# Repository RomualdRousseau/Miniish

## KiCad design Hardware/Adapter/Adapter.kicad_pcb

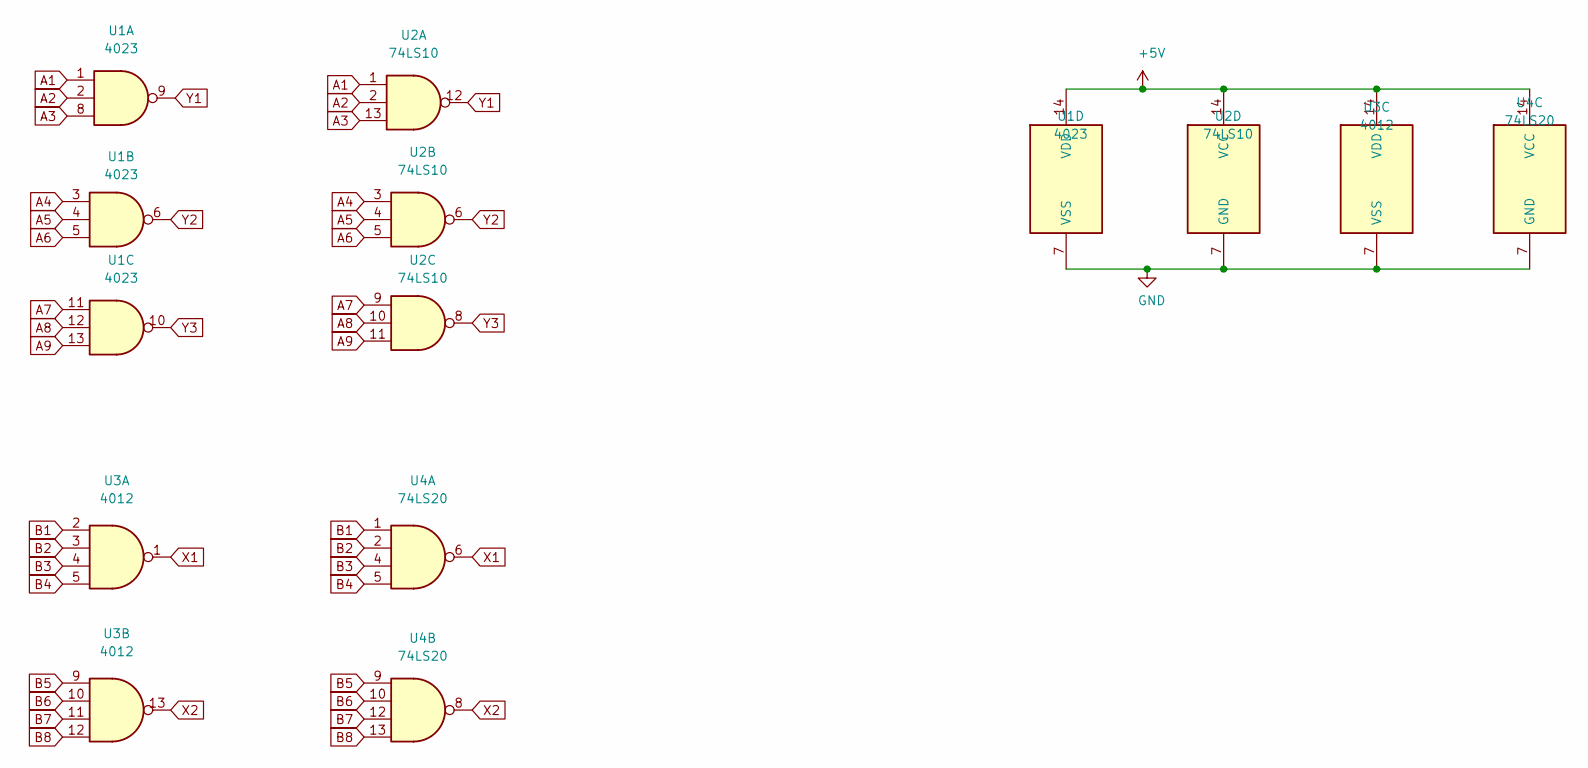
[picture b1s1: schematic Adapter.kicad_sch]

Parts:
U1: 4023; DIP-14_W7.62mm
U2: 74LS10; DIP-14_W7.62mm
U3: 4012; DIP-14_W7.62mm
U4: 74LS20; DIP-14_W7.62mm

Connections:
+5V: U1.14 (VDD), U2.14 (VCC), U3.14 (VDD), U4.14 (VCC)
A1: U1.1, U2.1
A2: U1.2, U2.2
A3: U1.8, U2.13
A4: U1.3, U2.3
A5: U1.4, U2.4
A6: U1.5, U2.5
A7: U1.11, U2.9
A8: U1.12, U2.10
A9: U1.13, U2.11
B1: U3.2, U4.1
B2: U3.3, U4.2
B3: U3.4, U4.4
B4: U3.5, U4.5
B5: U3.9, U4.9
B6: U3.10, U4.10
B7: U3.11, U4.12
B8: U3.12, U4.13
GND: U1.7 (VSS), U2.7 (GND), U3.7 (VSS), U4.7 (GND)
X1: U3.1, U4.6
X2: U3.13, U4.8
Y1: U1.9, U2.12
Y2: U1.6, U2.6
Y3: U1.10, U2.8

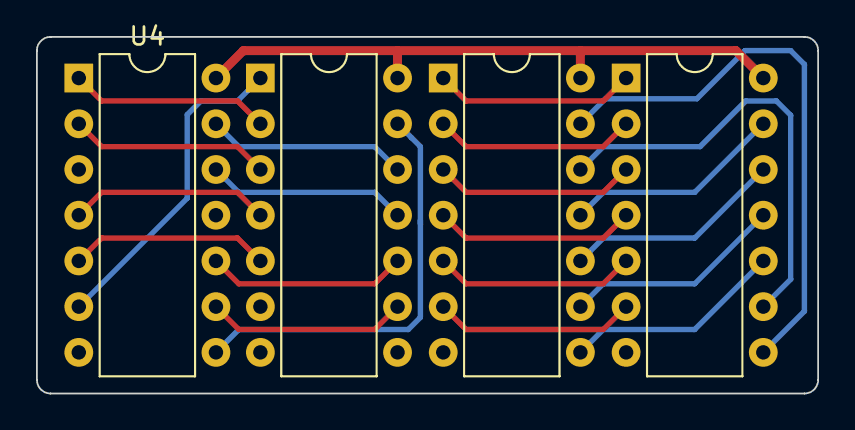
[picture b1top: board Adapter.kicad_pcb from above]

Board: 2 copper layers, 43.4 x 19.8 mm, 4 parts (0 on the bottom side), 24 nets.

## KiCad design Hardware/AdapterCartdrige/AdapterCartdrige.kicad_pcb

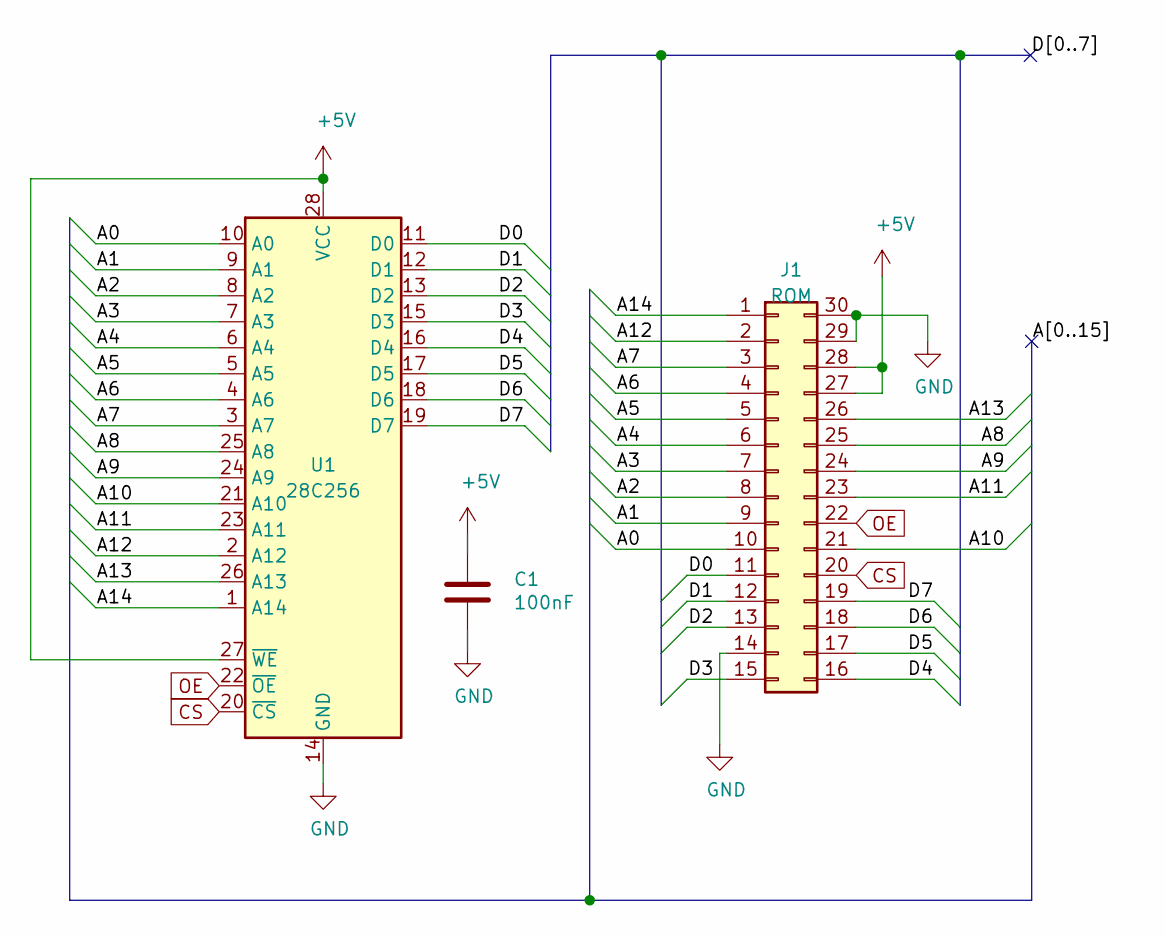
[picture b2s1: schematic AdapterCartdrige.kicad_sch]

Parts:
C1: 100nF; C_Disc_D5.0mm_W2.5mm_P2.50mm
J1: ROM; PinHeader_2x15_P2.54mm_Horizontal
U1: 28C256; DIP-28_W15.24mm

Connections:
+5V: C1.1, J1.27, J1.28, U1.27 (~WE), U1.28 (VCC)
/A0: J1.10, U1.10 (A0)
/A1: J1.9, U1.9 (A1)
/A2: J1.8, U1.8 (A2)
/A3: J1.7, U1.7 (A3)
/A4: J1.6, U1.6 (A4)
/A5: J1.5, U1.5 (A5)
/A6: J1.4, U1.4 (A6)
/A7: J1.3, U1.3 (A7)
/A8: J1.25, U1.25 (A8)
/A9: J1.24, U1.24 (A9)
/A10: J1.21, U1.21 (A10)
/A11: J1.23, U1.23 (A11)
/A12: J1.2, U1.2 (A12)
/A13: J1.26, U1.26 (A13)
/A14: J1.1, U1.1 (A14)
/D0: J1.11, U1.11 (D0)
/D1: J1.12, U1.12 (D1)
/D2: J1.13, U1.13 (D2)
/D3: J1.15, U1.15 (D3)
/D4: J1.16, U1.16 (D4)
/D5: J1.17, U1.17 (D5)
/D6: J1.18, U1.18 (D6)
/D7: J1.19, U1.19 (D7)
CS: J1.20, U1.20 (~CS)
GND: C1.2, J1.14, J1.29, J1.30, U1.14 (GND)
OE: J1.22, U1.22 (~OE)

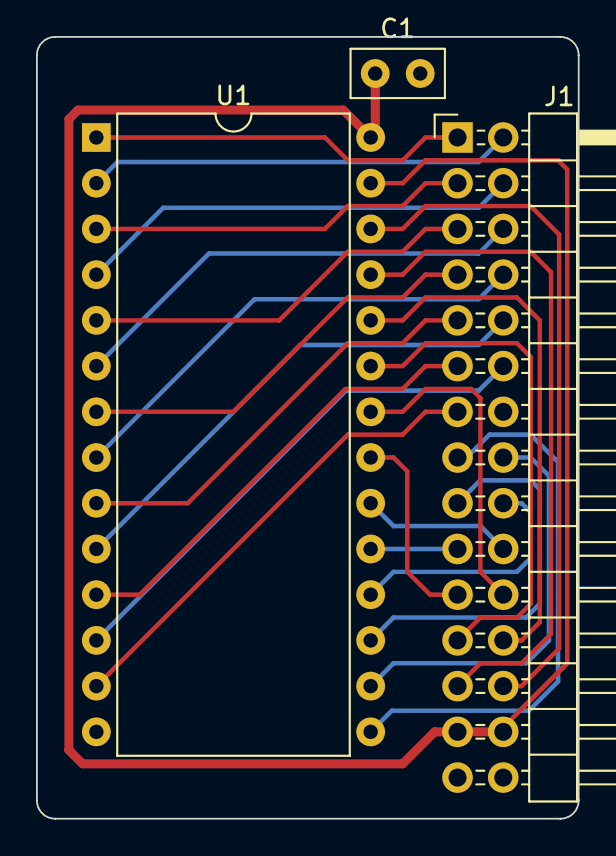
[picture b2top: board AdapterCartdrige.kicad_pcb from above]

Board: 2 copper layers, 30.1 x 43.4 mm, 3 parts (0 on the bottom side), 27 nets.

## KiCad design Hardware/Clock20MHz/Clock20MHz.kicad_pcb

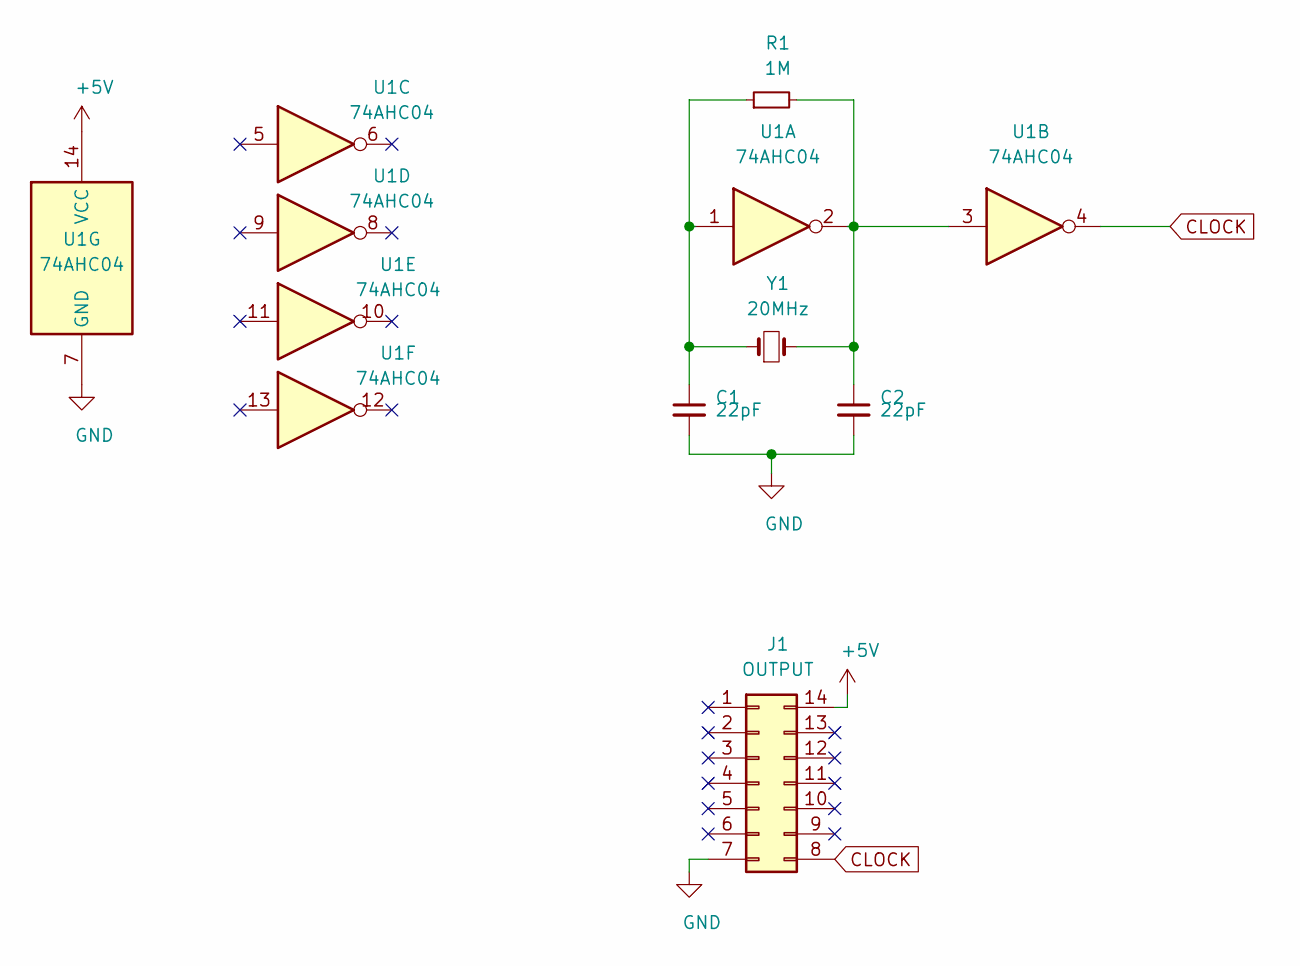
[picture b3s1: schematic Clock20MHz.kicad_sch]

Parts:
C1, C2: 22pF; C_Disc_D5.0mm_W2.5mm_P2.50mm
J1: OUTPUT; DIP-14_W7.62mm
R1: 1M; R_Axial_DIN0207_L6.3mm_D2.5mm_P10.16mm_Horizontal
U1: 74AHC04
Y1: 20MHz; Crystal_HC18-U_Vertical

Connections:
+5V: J1.14, U1.14 (VCC)
CLOCK: J1.8, U1.4
GND: C1.2, C2.2, J1.7, U1.7 (GND)
unnamed: C1.1, R1.1, U1.1, Y1.1
unnamed: C2.1, R1.2, U1.2, U1.3, Y1.2
no_connect_6: J1.1
no_connect_7: J1.10
no_connect_8: J1.11
no_connect_9: J1.12
no_connect_10: J1.13
no_connect_11: J1.2
no_connect_12: J1.3
no_connect_13: J1.4
no_connect_14: J1.5
no_connect_15: J1.6
no_connect_16: J1.9
no_connect_17: U1.10
no_connect_18: U1.11
no_connect_19: U1.12
no_connect_20: U1.13
no_connect_21: U1.5
no_connect_22: U1.6
no_connect_23: U1.8
no_connect_24: U1.9

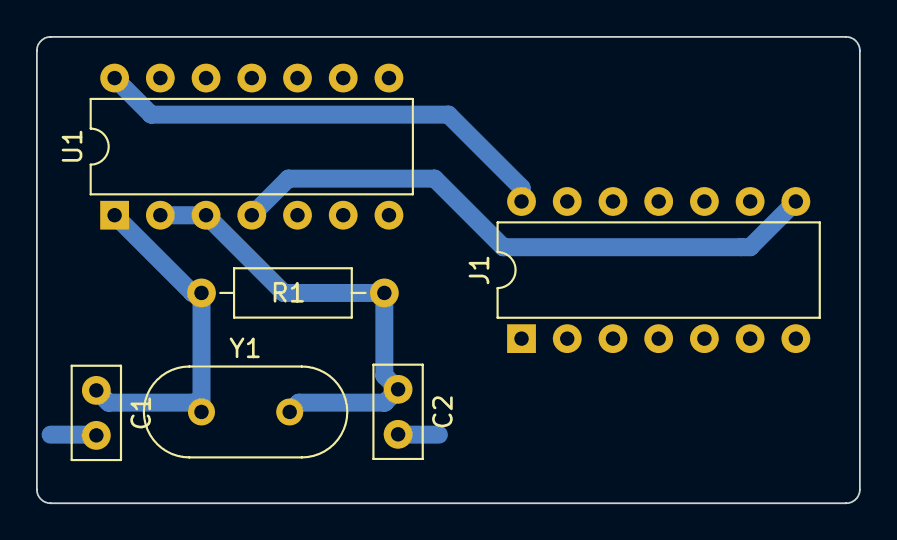
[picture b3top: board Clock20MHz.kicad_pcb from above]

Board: 2 copper layers, 45.7 x 25.9 mm, 6 parts (0 on the bottom side), 5 nets.

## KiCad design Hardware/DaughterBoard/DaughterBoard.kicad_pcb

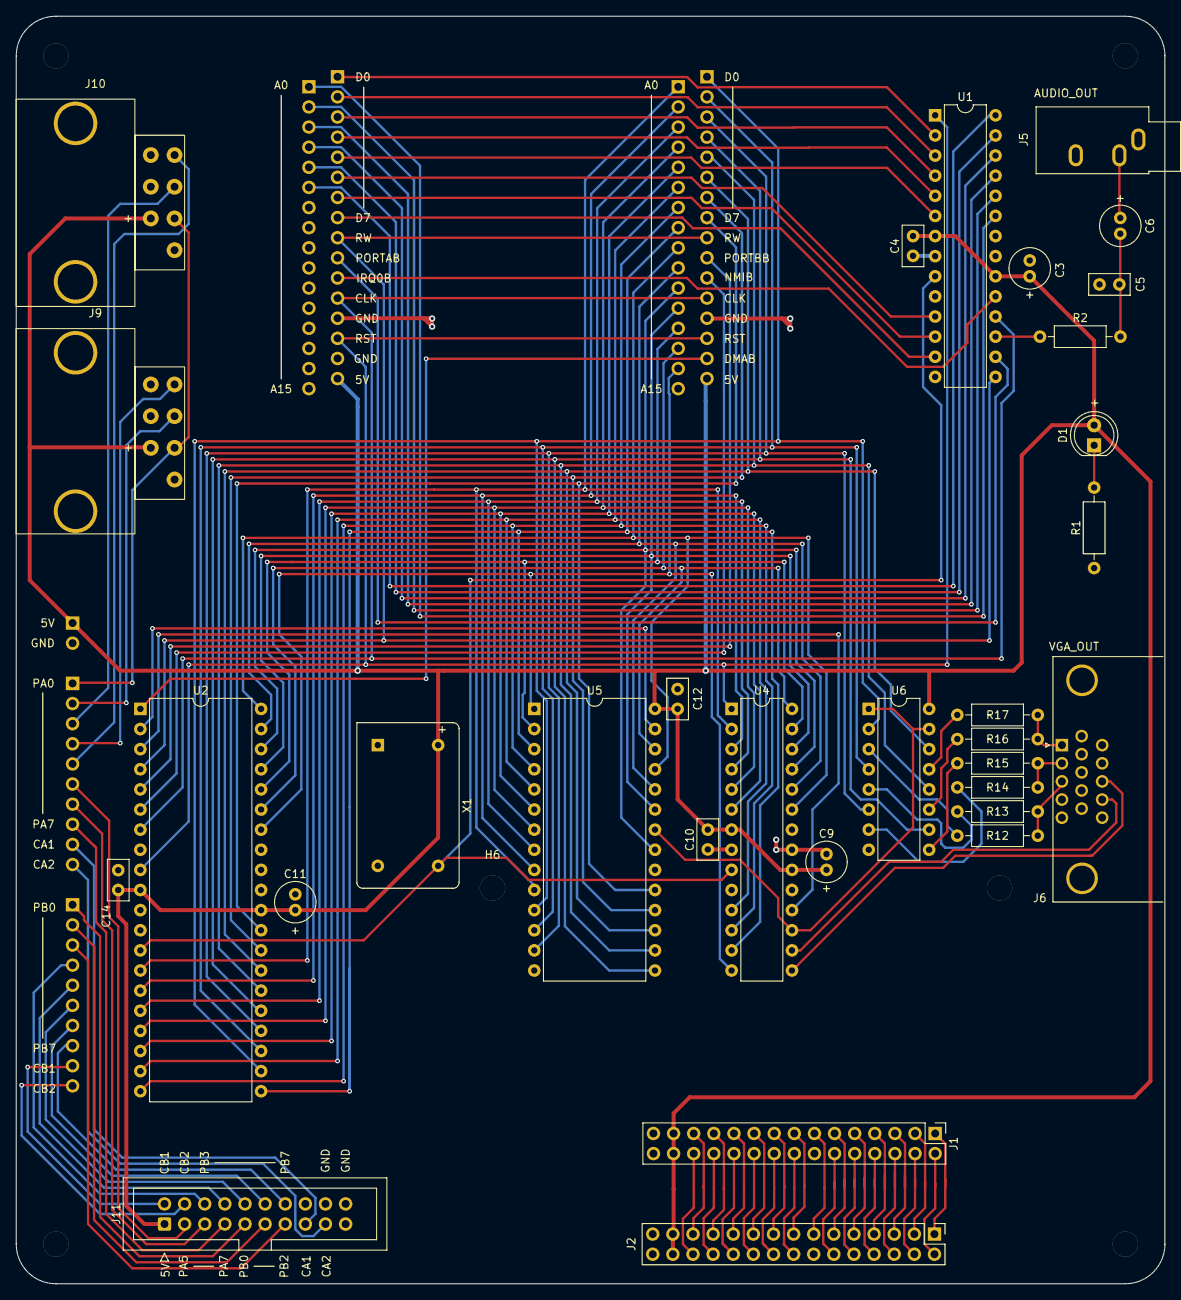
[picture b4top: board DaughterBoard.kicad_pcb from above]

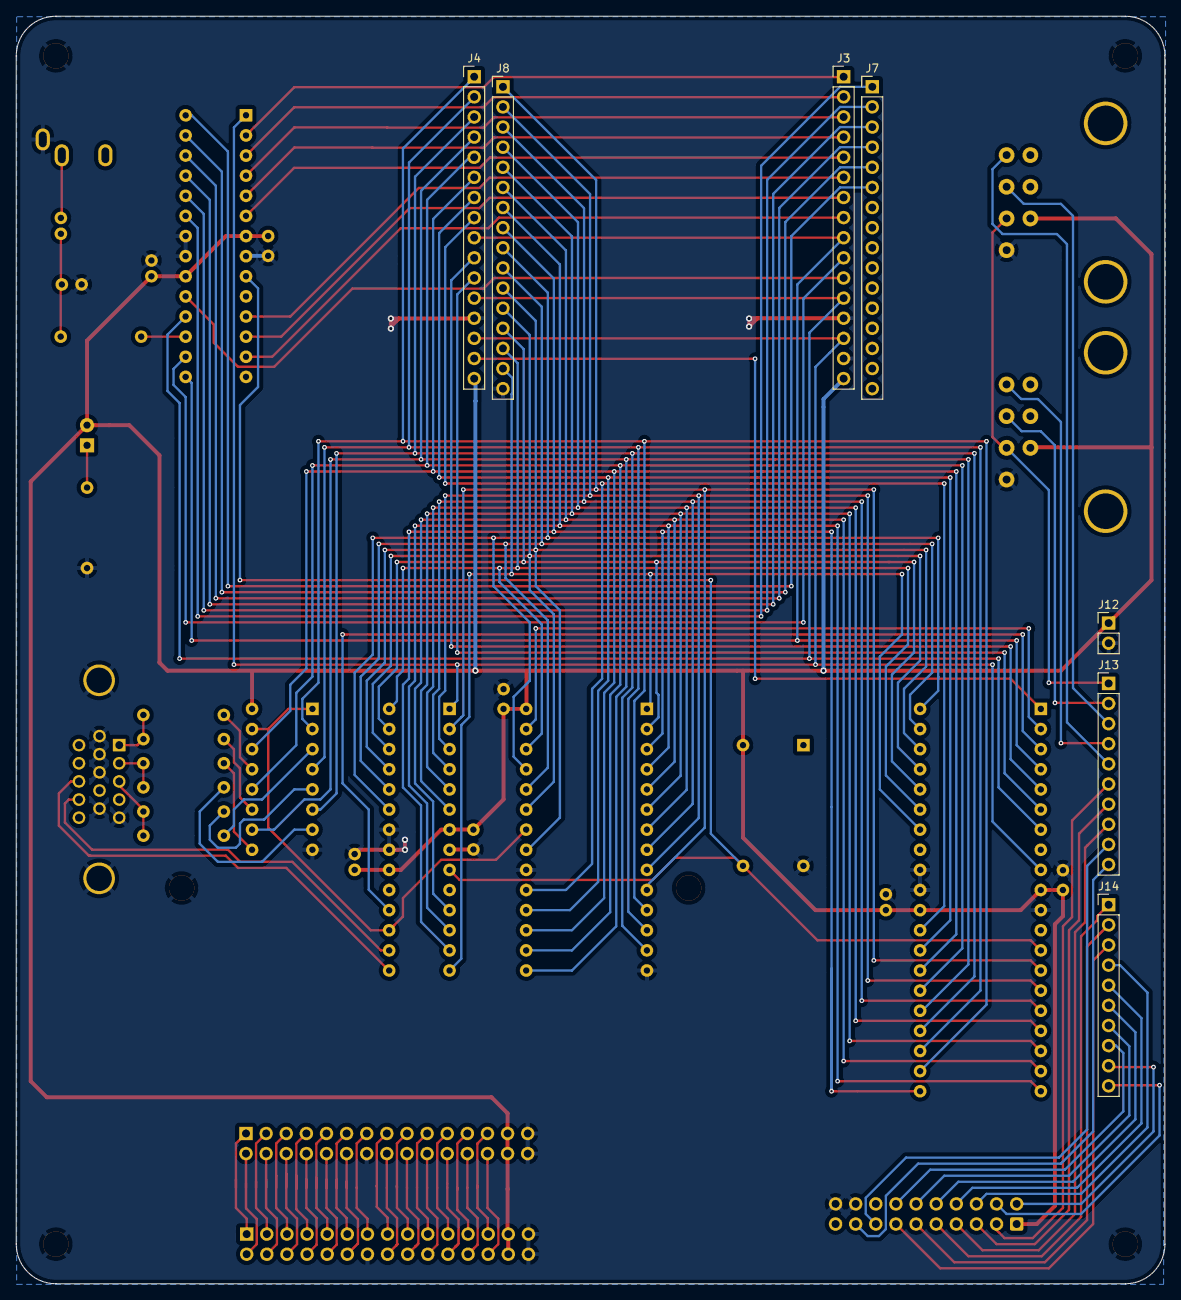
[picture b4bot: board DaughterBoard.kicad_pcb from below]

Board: 2 copper layers, 145.0 x 160.0 mm, 44 parts (7 on the bottom side), 111 nets.

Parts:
C3, C6, C9, C11: 10uF; C_Radial_D5.0mm_H11.0mm_P2.00mm
C4, C5, C10, C12, C14: 100nF; C_Disc_D5.0mm_W2.5mm_P2.50mm
D1: LED; LED_D5.0mm
H1, H2, H3, H4, H5, H6: MountingHole_Pad; MountingHole_3.2mm_M3
J1: CARTDRIGE; PinHeader_2x15_P2.54mm_Vertical
J2: ROM; PinHeader_2x15_P2.54mm_Vertical
J3: ISA00; PinHeader_1x16_P2.54mm_Vertical
J4: ISA10; PinHeader_1x16_P2.54mm_Vertical
J5: AUDIO_OUT; Jack_3.5mm_CUI_SJ1-3533NG_Horizontal
J6: VGA_OUT; DSUB-15-HD_Female_Horizontal_P2.29x1.98mm_EdgePinOffset8.35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
J7: ISA01; PinHeader_1x16_P2.54mm_Vertical
J8: ISA11; PinHeader_1x16_P2.54mm_Vertical
J9: JOYPAD1; NES_JoyPad
J10: JOYPAD2; NES_JoyPad
J11: LCD; IDC-Header_2x10_P2.54mm_Vertical
J12: POWER; PinHeader_1x02_P2.54mm_Vertical
J13: PA; PinHeader_1x10_P2.54mm_Vertical
J14: PB; PinHeader_1x10_P2.54mm_Vertical
R1: 220; R_Axial_DIN0207_L6.3mm_D2.5mm_P10.16mm_Horizontal
R2: 1K; R_Axial_DIN0207_L6.3mm_D2.5mm_P10.16mm_Horizontal
R12, R14, R16: 1.5K; R_Axial_DIN0207_L6.3mm_D2.5mm_P10.16mm_Horizontal
R13, R15, R17: 680; R_Axial_DIN0207_L6.3mm_D2.5mm_P10.16mm_Horizontal
U1, U4: ATmega328P-PU; DIP-28_W7.62mm
U2: ATmega1284P-PU; DIP-40_W15.24mm
U5: AS6C62256; DIP-28_W15.24mm
U6: 74HC365; DIP-16_W7.62mm
X1: ACO-20MHz; Oscillator_DIP-14

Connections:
+5V: C3.1, C4.1, C9.1, C10.1, C11.1, C12.1, C14.1, D1.2 (A), J1.27, J1.28, J2.27, J2.28, J3.16, J4.16, J9.7 (VCC), J10.7 (VCC), J11.1, J12.1, U1.7 (VCC), U1.20 (AVCC), U2.10 (VCC), U2.30 (AVCC), U4.7 (VCC), U4.20 (AVCC), U5.28 (VCC), U6.16 (VCC), X1.14 (Vcc)
/AA0: J7.1, U1.23 (PC0)
/AA1: J7.2, U1.24 (PC1)
/AA2: J7.3, U1.25 (PC2)
/AA3: J7.4, U1.26 (PC3)
/AA4: J7.5, U1.27 (PC4)
/AA5: J7.6, U1.28 (PC5)
/AB0: J8.1, U2.14 (PD0), U4.2 (PD0), U5.10 (A0)
/AB1: J8.2, U2.15 (PD1), U4.3 (PD1), U5.9 (A1)
/AB2: J8.3, U2.16 (PD2), U4.4 (PD2), U5.8 (A2)
/AB3: J8.4, U2.17 (PD3), U4.5 (PD3), U5.7 (A3)
/AB4: J8.5, U2.18 (PD4), U4.6 (PD4), U5.6 (A4)
/AB5: J8.6, U2.19 (PD5), U4.11 (PD5), U5.5 (A5)
/AB6: J8.7, U2.20 (PD6), U4.12 (PD6), U5.4 (A6)
/AB7: J8.8, U2.21 (PD7), U4.13 (PD7), U5.3 (A7)
/AB8: J8.9, U2.40 (PA0), U4.23 (PC0), U5.25 (A8)
/AB9: J8.10, U2.39 (PA1), U4.24 (PC1), U5.24 (A9)
/AB10: J8.11, U2.38 (PA2), U4.25 (PC2), U5.21 (A10)
/AB11: J8.12, U2.37 (PA3), U4.26 (PC3), U5.23 (A11)
/AB12: J8.13, U2.36 (PA4), U4.27 (PC4), U5.2 (A12)
/AB13: J8.14, U2.35 (PA5), U4.28 (PC5), U5.26 (A13)
/AB14: J8.15, U2.34 (PA6), U4.14 (PB0), U5.1 (A14)
/CLOCK: J3.12, J4.12, U1.18 (PB4), U2.7 (PB6)
/DA0: J3.1, U1.2 (PD0)
/DA1: J3.2, U1.3 (PD1)
/DA2: J3.3, U1.4 (PD2)
/DA3: J3.4, U1.5 (PD3)
/DA4: J3.5, U1.6 (PD4)
/DA5: J3.6, U1.11 (PD5)
/DA6: J3.7, U1.12 (PD6)
/DA7: J3.8, U1.13 (PD7)
/DB0: J4.1, U2.22 (PC0), U5.11 (Q0), U6.2 (I1)
/DB1: J4.2, U2.23 (PC1), U5.12 (Q1), U6.4 (I2)
/DB2: J4.3, U2.24 (PC2), U5.13 (Q2), U6.6 (I3)
/DB3: J4.4, U2.25 (PC3), U5.15 (Q3), U6.10 (I4)
/DB4: J4.5, U2.26 (PC4), U5.16 (Q4), U6.12 (I5)
/DB5: J4.6, U2.27 (PC5), U5.17 (Q5), U6.14 (I6)
/DB6: J4.7, U2.28 (PC6), U5.18 (Q6)
/DB7: J4.8, U2.29 (PC7), U5.19 (Q7)
/DMAB: J4.15, U2.1 (PB0)
/IRQ0B: J3.11, U1.19 (PB5)
/NMIB: J4.11, U2.6 (PB5)
/PORTAB: J3.10, U1.16 (PB2)
/PORTBB: J4.10, U2.5 (PB4)
/RW: J3.9, J4.9, U1.15 (PB1), U2.4 (PB3)
AUDIO: R2.1, U1.17 (PB3)
BLUE: J6.3, R12.1, R13.1
CA1: J11.15, J13.9
CA2: J11.17, J13.10
CB1: J11.2, J14.9
CB2: J11.4, J14.10
CLOCK2: U1.9 (XTAL1/PB6), U2.13 (XTAL1), U4.9 (XTAL1/PB6), X1.8 (OUT)
GND: C3.2, C4.2, C5.2, C9.2, C10.2, C11.2, C12.2, C14.2, H1.1, H2.1, H3.1, H4.1, H5.1, J1.14, J1.29, J1.30, J2.14, J2.29, J2.30, J3.13, J3.15, J4.13, J5.S, J6.0, J6.5, J6.6, J6.7, J6.8, J6.10, J8.16, J9.1 (GND), J10.1 (GND), J11.18, J11.20, J12.2, R1.2, U1.8 (GND), U1.21 (AREF), U1.22 (GND), U2.11 (GND), U2.31 (GND), U2.32 (AREF), U4.8 (GND), U4.21 (AREF), U4.22 (GND), U5.14 (GND), U5.20 (~CS), U6.8 (GND), X1.7 (GND)
GREEN: J6.2, R14.1, R15.1
HLINE: U4.17 (PB3), U5.22 (~OE), U6.1 (E1), U6.15 (E2)
HSYNC: J6.13, U4.15 (PB1)
JP_CLOCK: J9.2 (CLOCK), J10.2 (CLOCK), J13.1
JP_DATA1: J9.4 (D1), J13.4
JP_DATA2: J10.4 (D1), J13.5
JP_LATCH1: J9.3 (LATCH), J13.2
JP_LATCH2: J10.3 (LATCH), J13.3
LCD_D0: J11.9, J14.1
LCD_D1: J11.11, J14.2
LCD_D2: J11.13, J14.3
LCD_D3: J11.6, J14.4
LCD_D4: J11.8, J14.5
LCD_D5: J11.10, J14.6
LCD_D6: J11.12, J14.7
LCD_D7: J11.14, J14.8
LCD_EN: J11.7, J13.8
LCD_RS: J11.3, J13.6
LCD_RW: J11.5, J13.7
unnamed: C5.1, C6.2, R2.2
unnamed: C6.1, J5.T
unnamed: D1.1 (K), R1.1
unnamed: J1.1, J2.1
unnamed: J1.2, J2.2
unnamed: J1.3, J2.3
unnamed: J1.4, J2.4
unnamed: J1.5, J2.5
unnamed: J1.6, J2.6
unnamed: J1.7, J2.7
unnamed: J1.8, J2.8
unnamed: J1.9, J2.9
unnamed: J1.10, J2.10
unnamed: J1.11, J2.11
unnamed: J1.12, J2.12
unnamed: J1.13, J2.13
unnamed: J1.15, J2.15
unnamed: J1.16, J2.16
unnamed: J1.17, J2.17
unnamed: J1.18, J2.18
unnamed: J1.19, J2.19
unnamed: J1.20, J2.20
unnamed: J1.21, J2.21
unnamed: J1.22, J2.22
unnamed: J1.23, J2.23
unnamed: J1.24, J2.24
unnamed: J1.25, J2.25
unnamed: J1.26, J2.26
unnamed: R12.2, U6.3 (O1)
unnamed: R13.2, U6.5 (O2)
unnamed: R14.2, U6.7 (O3)
unnamed: R15.2, U6.9 (O4)
unnamed: R16.2, U6.11 (O5)
unnamed: R17.2, U6.13 (O6)
RED: J6.1, R16.1, R17.1
RESET: J3.14, J4.14, U1.1 (~RESET~/PC6), U2.9 (~RESET), U4.1 (~RESET~/PC6)
VBLANK: U2.3 (PB2), U4.18 (PB4)
VSYNC: J6.14, U4.16 (PB2)
WRAM: U2.2 (PB1), U5.27 (~WE)

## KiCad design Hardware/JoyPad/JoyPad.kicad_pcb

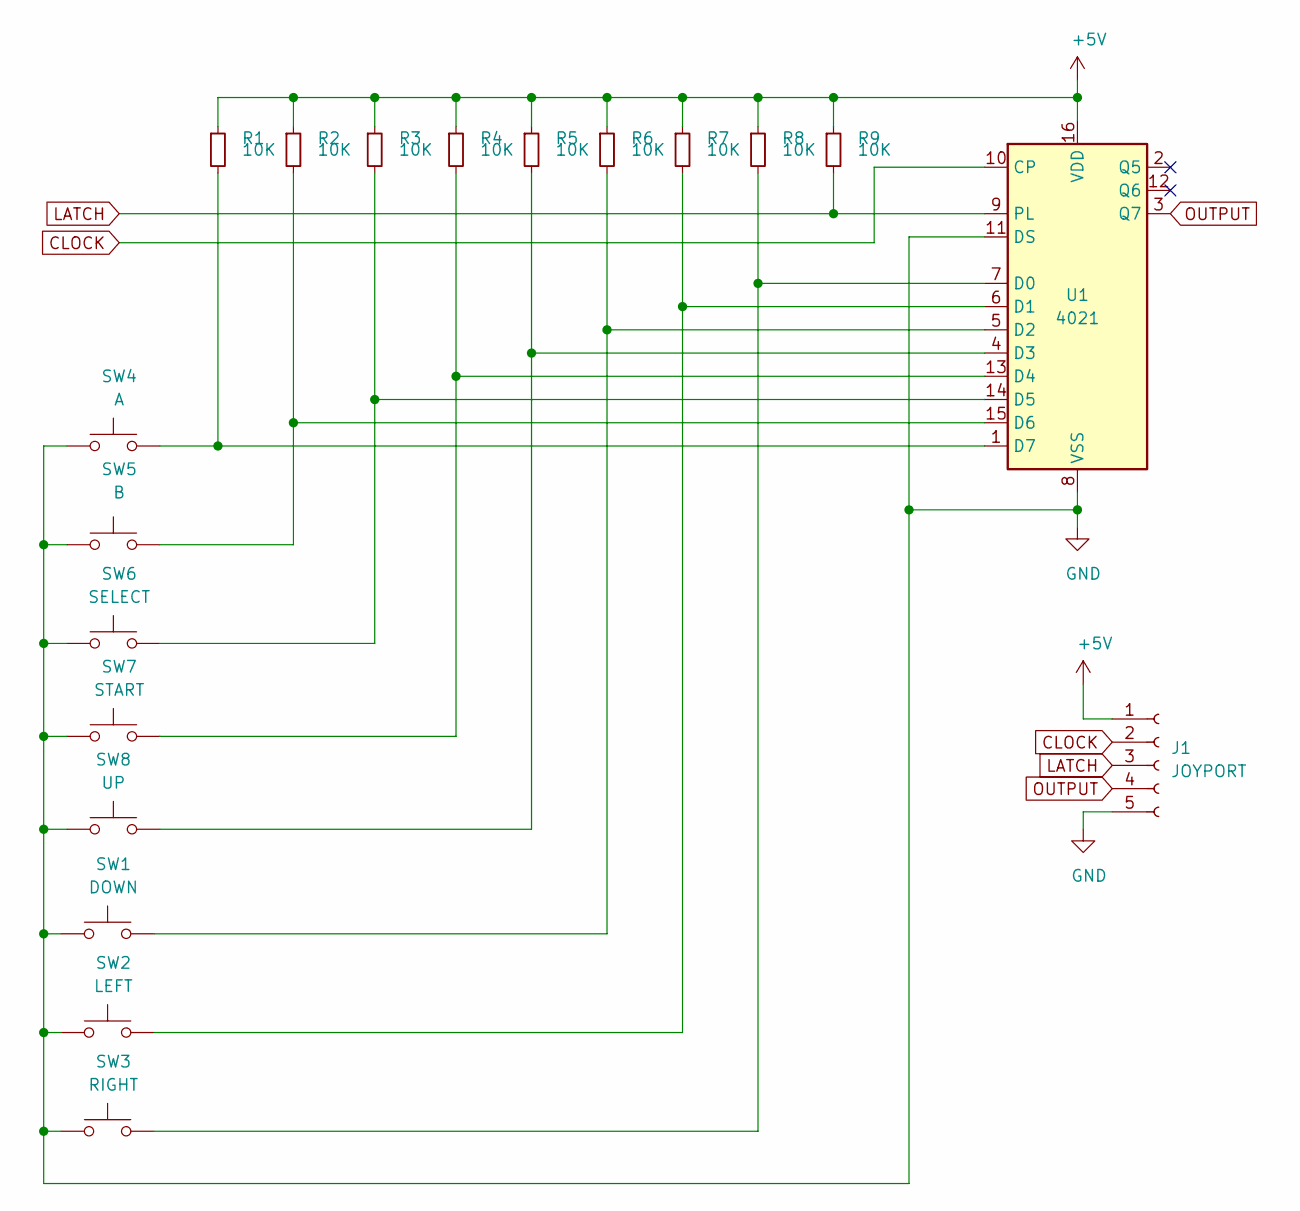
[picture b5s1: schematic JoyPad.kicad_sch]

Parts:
J1: JOYPORT; PinSocket_1x05_P2.54mm_Vertical
R1, R2, R3, R4, R5, R6, R7, R8, R9: 10K; R_Axial_DIN0207_L6.3mm_D2.5mm_P10.16mm_Horizontal
SW1: DOWN; SW_PUSH-12mm
SW2: LEFT; SW_PUSH-12mm
SW3: RIGHT; SW_PUSH-12mm
SW4: A; SW_PUSH-12mm
SW5: B; SW_PUSH-12mm
SW6: SELECT; SW_PUSH-12mm
SW7: START; SW_PUSH-12mm
SW8: UP; SW_PUSH-12mm
U1: 4021; DIP-16_W7.62mm

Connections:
+5V: J1.1, R1.1, R2.1, R3.1, R4.1, R5.1, R6.1, R7.1, R8.1, R9.1, U1.16 (VDD)
CLOCK: J1.2, U1.10 (CP)
GND: J1.5, SW1.1, SW2.1, SW3.1, SW4.1, SW5.1, SW6.1, SW7.1, SW8.1, U1.8 (VSS), U1.11 (DS)
LATCH: J1.3, R9.2, U1.9 (PL)
unnamed: R1.2, SW4.2, U1.1 (D7)
unnamed: R2.2, SW5.2, U1.15 (D6)
unnamed: R3.2, SW6.2, U1.14 (D5)
unnamed: R4.2, SW7.2, U1.13 (D4)
unnamed: R5.2, SW8.2, U1.4 (D3)
unnamed: R6.2, SW1.2, U1.5 (D2)
unnamed: R7.2, SW2.2, U1.6 (D1)
unnamed: R8.2, SW3.2, U1.7 (D0)
OUTPUT: J1.4, U1.3 (Q7)
no_connect_14: U1.12 (Q6)
no_connect_15: U1.2 (Q5)

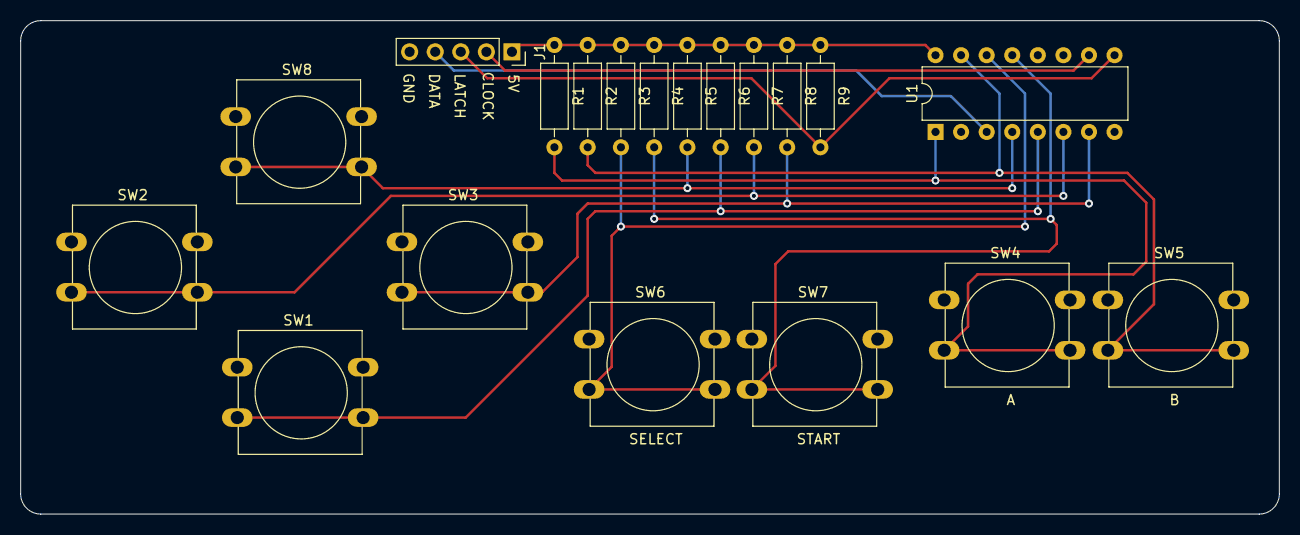
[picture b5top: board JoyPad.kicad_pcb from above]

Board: 2 copper layers, 125.0 x 49.0 mm, 19 parts (0 on the bottom side), 13 nets.
